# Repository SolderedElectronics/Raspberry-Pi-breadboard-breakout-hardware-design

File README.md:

# Raspberry Pi breadboard breakout + cable Hardware Design

## About the Product

|  |
| :----------------------------------------------------------: |
| [Buy Raspberry Pi breadboard breakout + cable](https://www.solde.red/333135) |

With the Raspberry Pi breadboard breakout board, you can easily connect your Raspberry Pi with a regular breadboard. It fits on standard half-size and full-size breadboards. It even adds a couple of ground and power supply pins. Best of all, the pins are already soldered. You just have to plug the cable in. This breakout will get you prototyping on the Raspberry Pi in no time!

---

## Repository Contents

This repository contains all design files for Raspberry Pi breadboard breakout + cable, organized as follows:

- **`CAD` folder**: Contains KiCAD design files, including:
  - Schematics
  - PCB layout
  - Panel PCB layout
  - Source 3D files in Fusion360, if any
  - All files are sorted by version with a detailed change log.
- **`OUTPUTS` folder**: Includes all production-ready files, such as:
  - Bill of Materials (BOM) and interactive BOM (iBOM)
  - PDF versions of schematics
  - 3D `.step` file of the board
  - 3D-printable models
  - Gerber files for PCB manufacturing
  - Image of the pinout of the board
  - Product image
  - Compliance, legal and generic sales documents

Refer to the `Change Log` in the CAD folder for details about updates between versions.

---

## Learn More About the Product

Beyond the repository, explore the following resources:

### Soldered Verify

The **Soldered Verify** system ensures every board you purchase from Soldered is fully functional. It also provides access to exclusive test data for your product. To get started, find the unique Soldered Verify ID on your product's packaging and enter the ID on the [Soldered Verify page](https://soldered.com/verify/) to access test results and additional product details.

### Soldered Community

Soldered Community is your go-to place for technical support. Our engineers track and answer all questions posted there, and it’s a great space for the maker community. Get answers to your questions and solutions for your challenges at [Soldered Community](https://soldered.com/community).

### solde.red

solde.red is an ultimate URL shortener and information hub. Access it by typing solde.red/ followed by your product SKU, e.g., [solde.red/333000](https://solde.red/333000), to find getting-started guides, datasheets, open-source hardware and software files, certifications, images, pinouts, and more. Read more about the shortener [here](https://solde.red/info/).

---

## Contributing

Contributions are welcome! Here’s how you can get involved:

- Submit pull requests to enhance the design or fix issues.
- Report bugs or problems by opening an issue.

We encourage community collaboration to make this product even better.

---

## About Soldered

[Soldered for Makers](https://soldered.com) specializes in designing and manufacturing electronic products tailored for enthusiasts, ranging from hobbyists to professionals. Our portfolio includes electronic boards, sensors, and actuators that are widely utilized in fields such as microelectronics, mechatronics, robotics, programming, and IoT. Every product we offer is designed in-house and built upon open-source hardware and software platforms. Proudly certified and manufactured within the European Union, our catalog likely includes the product you need for your project.

We complement these products with comprehensive tutorials and manuals, product descriptions, schematics, programming codes, and project examples. Our round-the-clock [customer and technical support](https://soldered.com/community) is available for all our products, irrespective of the sales channel. Soldered’s success and services reflect our maker community’s unwavering [trust](https://www.trustpilot.com/review/soldered.com), for which we are deeply grateful. Join our community and create using Soldered products.

---

## License

All Soldered open-source hardware (OSH) is under The TAPR Open Hardware License. Read more in the LICENSE file located in this repository.

**Disclaimer:**

No warranty - all designs in this repository are distributed in the hope that they will be useful, but without any warranty. They are provided "AS IS", therefore without warranty of any kind, either expressed or implied. The entire quality and performance of what you do with the contents of this repository are your responsibility. In no event Soldered Electronics will be liable for your damages, or losses, including any general, special, incidental, or consequential damage arising out of the use or inability to use the contents of this repository. 

---

## Have fun!

Thank you for your support from your fellow makers at Soldered Electronics.

Happy Making!

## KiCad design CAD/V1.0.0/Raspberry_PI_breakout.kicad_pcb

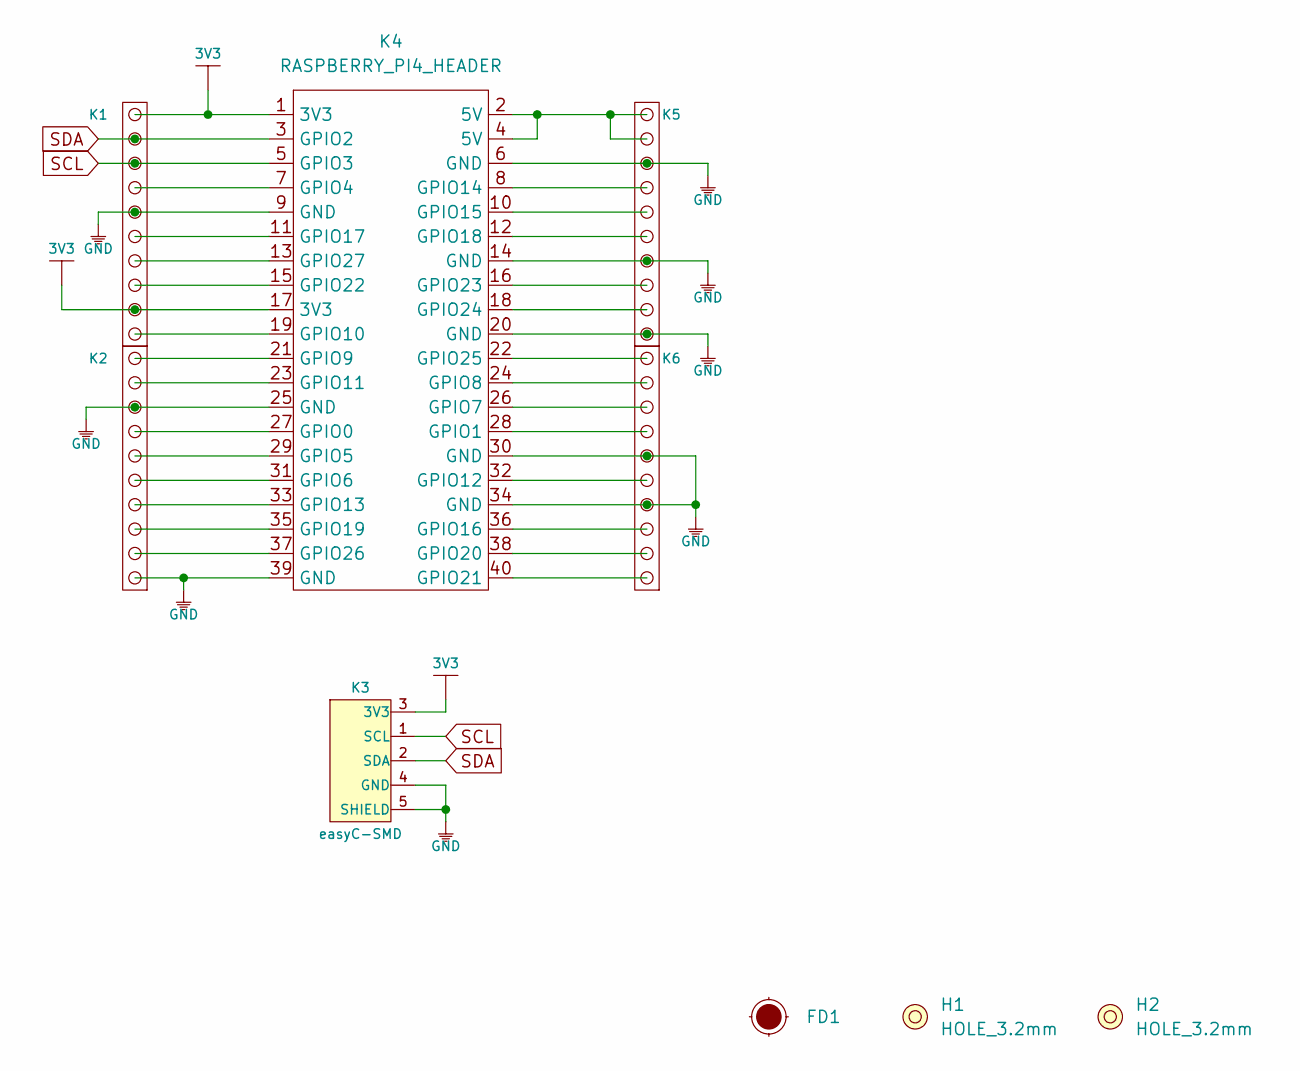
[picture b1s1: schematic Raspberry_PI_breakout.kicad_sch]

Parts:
FD1: Fiducial_Stencil; FIDUCIAL_1MM_PASTE
H1, H2: HOLE_3.2mm
K1, K2, K5, K6: HEADER_MALE_10X1
K3: easyC-SMD; easyC-connector
K4: RASPBERRY_PI4_HEADER

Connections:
3V3: K1.2, K1.10, K3.3 (3V3), K4.1 (3V3), K4.17 (3V3)
GND: K1.6, K2.1, K2.8, K3.4 (GND), K3.5 (SHIELD), K4.6 (GND), K4.9 (GND), K4.14 (GND), K4.20 (GND), K4.25 (GND), K4.30 (GND), K4.34 (GND), K4.39 (GND), K5.1, K5.4, K5.8, K6.4, K6.6
unnamed: K1.1, K4.19 (GPIO10)
unnamed: K1.3, K4.15 (GPIO22)
unnamed: K1.4, K4.13 (GPIO27)
unnamed: K1.5, K4.11 (GPIO17)
unnamed: K1.7, K4.7 (GPIO4)
unnamed: K2.2, K4.37 (GPIO26)
unnamed: K2.3, K4.35 (GPIO19)
unnamed: K2.4, K4.33 (GPIO13)
unnamed: K2.5, K4.31 (GPIO6)
unnamed: K2.6, K4.29 (GPIO5)
unnamed: K2.7, K4.27 (GPIO0)
unnamed: K2.9, K4.23 (GPIO11)
unnamed: K2.10, K4.21 (GPIO9)
unnamed: K4.2 (5V), K4.4 (5V), K5.9, K5.10
unnamed: K4.8 (GPIO14), K5.7
unnamed: K4.10 (GPIO15), K5.6
unnamed: K4.12 (GPIO18), K5.5
unnamed: K4.16 (GPIO25), K5.3
unnamed: K4.18 (GPIO24), K5.2
unnamed: K4.22 (GPIO25), K6.10
unnamed: K4.24 (GPIO8), K6.9
unnamed: K4.26 (GPIO7), K6.8
unnamed: K4.28 (GPIO1), K6.7
unnamed: K4.32 (GPIO12), K6.5
unnamed: K4.36 (GPIO16), K6.3
unnamed: K4.38 (GPIO20), K6.2
unnamed: K4.40 (GPIO21), K6.1
SCL: K1.8, K3.1 (SCL), K4.5 (GPIO3)
SDA: K1.9, K3.2 (SDA), K4.3 (GPIO2)

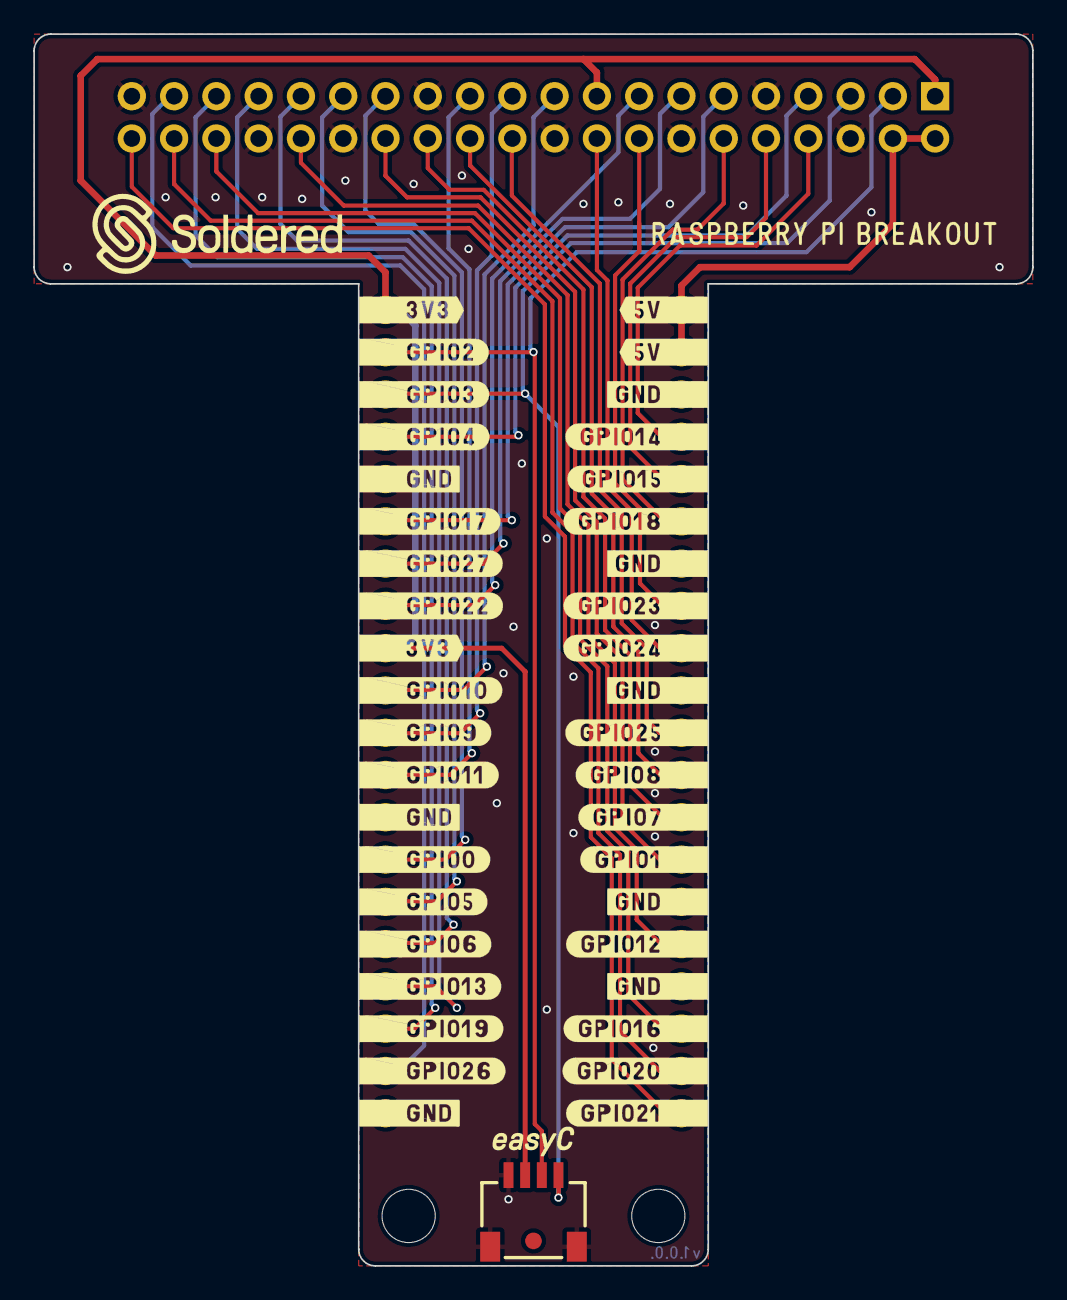
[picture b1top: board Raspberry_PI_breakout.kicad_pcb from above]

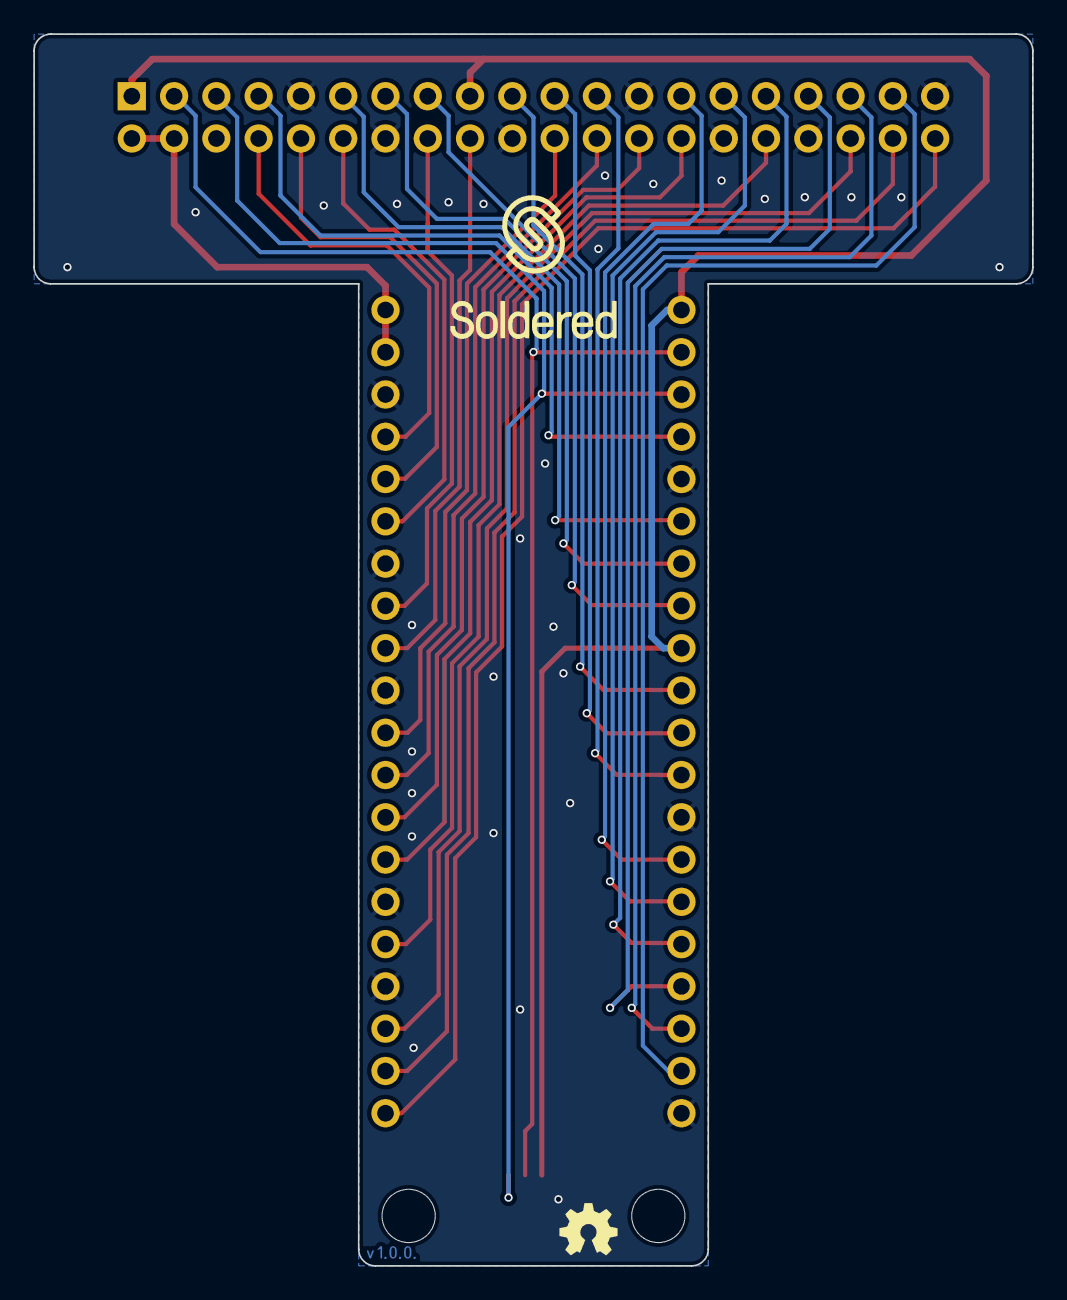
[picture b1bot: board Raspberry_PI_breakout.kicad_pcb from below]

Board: 2 copper layers, 60.0 x 74.0 mm, 9 parts (4 on the bottom side), 31 nets.

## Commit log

2022-08-06 Updating open source files.
